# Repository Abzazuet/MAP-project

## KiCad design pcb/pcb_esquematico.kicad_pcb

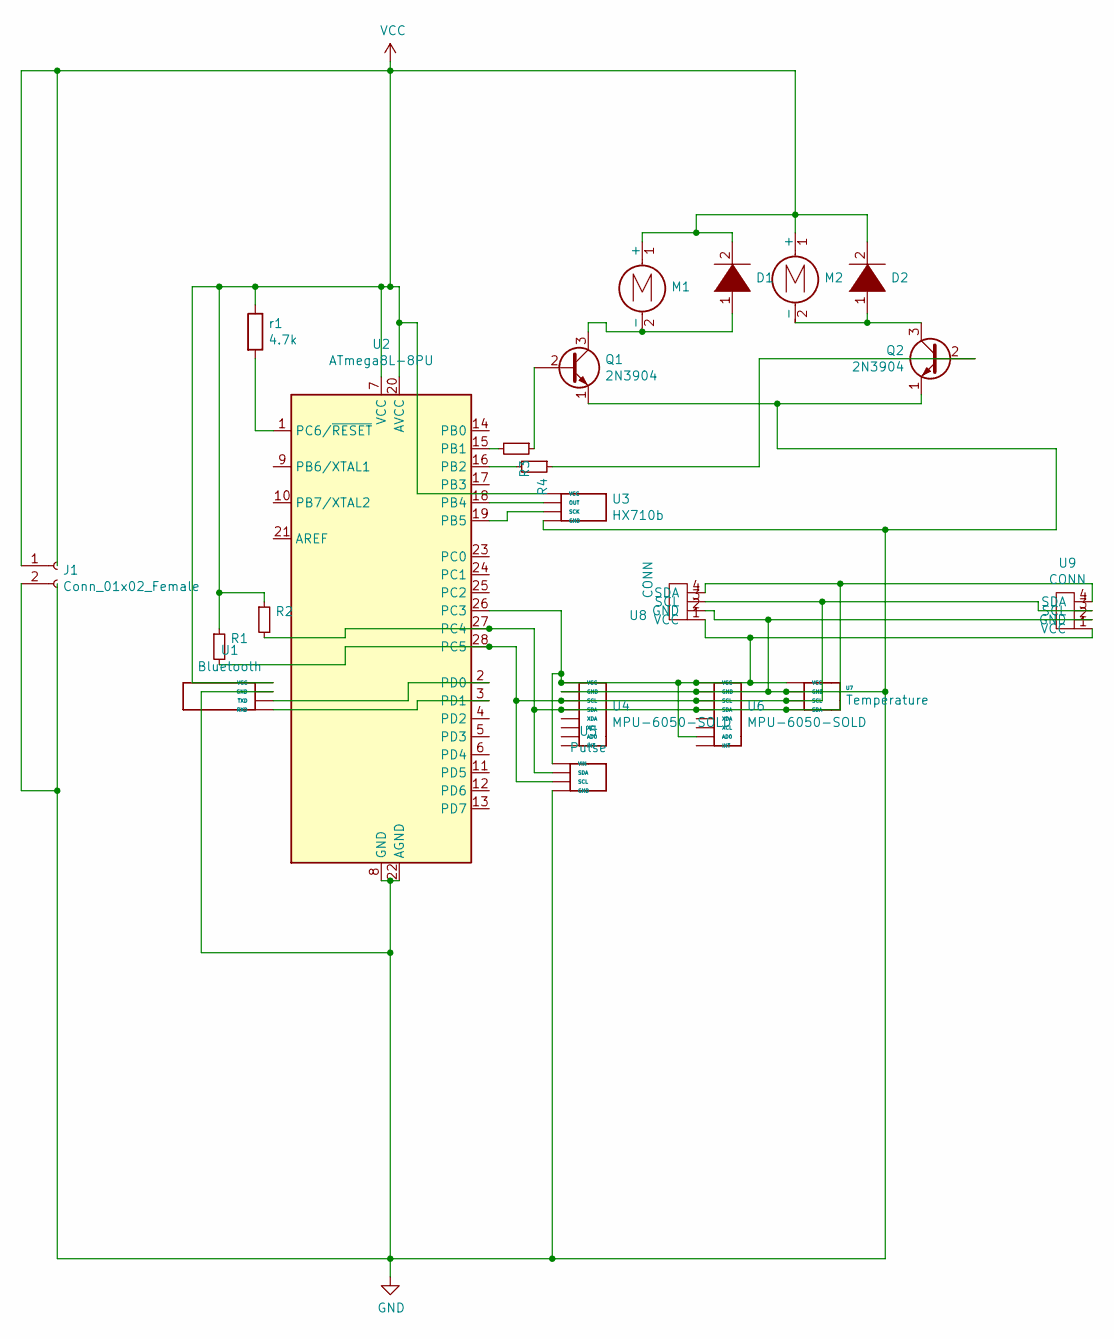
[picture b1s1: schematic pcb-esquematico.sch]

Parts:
D1: DIODE; D_DO-41_SOD81_P5.08mm_Vertical_KathodeUp
D2: DIODE; D_DO-41_SOD81_P5.08mm_Vertical_AnodeUp
J1: Conn_01x02_Female; JWT_A3963_1x02_P3.96mm_Vertical
M1, M2: Motor_DC; PinHeader_1x02_P2.54mm_Horizontal
Q1, Q2: 2N3904; TO-92_HandSolder
R1, R2: 4700; R_Axial_DIN0309_L9.0mm_D3.2mm_P12.70mm_Horizontal
R3, R4: 1000; R_Axial_DIN0309_L9.0mm_D3.2mm_P12.70mm_Horizontal
U1: Bluetooth; PinHeader_1x04_P2.54mm_Vertical
U2: ATmega8L-8PU; DIP-28_W7.62mm
U3: HX710b; PinHeader_1x04_P2.54mm_Vertical
U4, U6: MPU-6050-SOLD; PinHeader_1x08_P2.54mm_Vertical
U5: Pulse; PinHeader_1x04_P2.54mm_Vertical
U7: Temperature; PinHeader_1x04_P2.54mm_Vertical
U8, U9: CONN; PinSocket_1x04_P2.54mm_Horizontal
r1: 4.7k; R_Axial_DIN0309_L9.0mm_D3.2mm_P12.70mm_Horizontal

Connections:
GND: J1.2, Q1.1 (E), Q2.1 (E), U1.2 (GND), U2.8 (GND), U2.22 (AGND), U3.4 (GND), U4.2 (GND), U5.4 (GND), U6.2 (GND), U7.2 (GND), U8.2 (GND), U9.2 (GND)
unnamed: D1.1 (K), M1.2 (-), Q1.3 (C)
unnamed: D2.1 (K), M2.2 (-), Q2.3 (C)
unnamed: Q1.2 (B), R3.1
unnamed: Q2.2 (B), R4.1
unnamed: R1.2, U2.28 (PC5), U4.3 (SCL), U5.3 (SCL), U6.3 (SCL), U7.3 (SCL), U8.3 (SCL), U9.3 (SCL)
unnamed: R2.2, U2.27 (PC4), U4.4 (SDA), U5.2 (SDA), U6.4 (SDA), U7.4 (SDA), U8.4 (SDA), U9.4 (SDA)
unnamed: R3.2, U2.15 (PB1)
unnamed: R4.2, U2.16 (PB2)
unnamed: U1.3 (TXD), U2.2 (PD0)
unnamed: U1.4 (RXD), U2.3 (PD1)
unnamed: U2.1 (PC6/~RESET), r1.2
unnamed: U2.18 (PB4), U3.2 (OUT)
unnamed: U2.19 (PB5), U3.3 (SCK)
unnamed: U2.26 (PC3), U4.1 (VCC), U5.1 (VIN), U6.1 (VCC), U6.7 (AD0), U7.1 (VCC), U8.1 (VCC), U9.1 (VCC)
VCC: D1.2 (A), D2.2 (A), J1.1, M1.1 (+), M2.1 (+), R1.1, R2.1, U1.1 (VCC), U2.7 (VCC), U2.20 (AVCC), U3.1 (VCC), r1.1

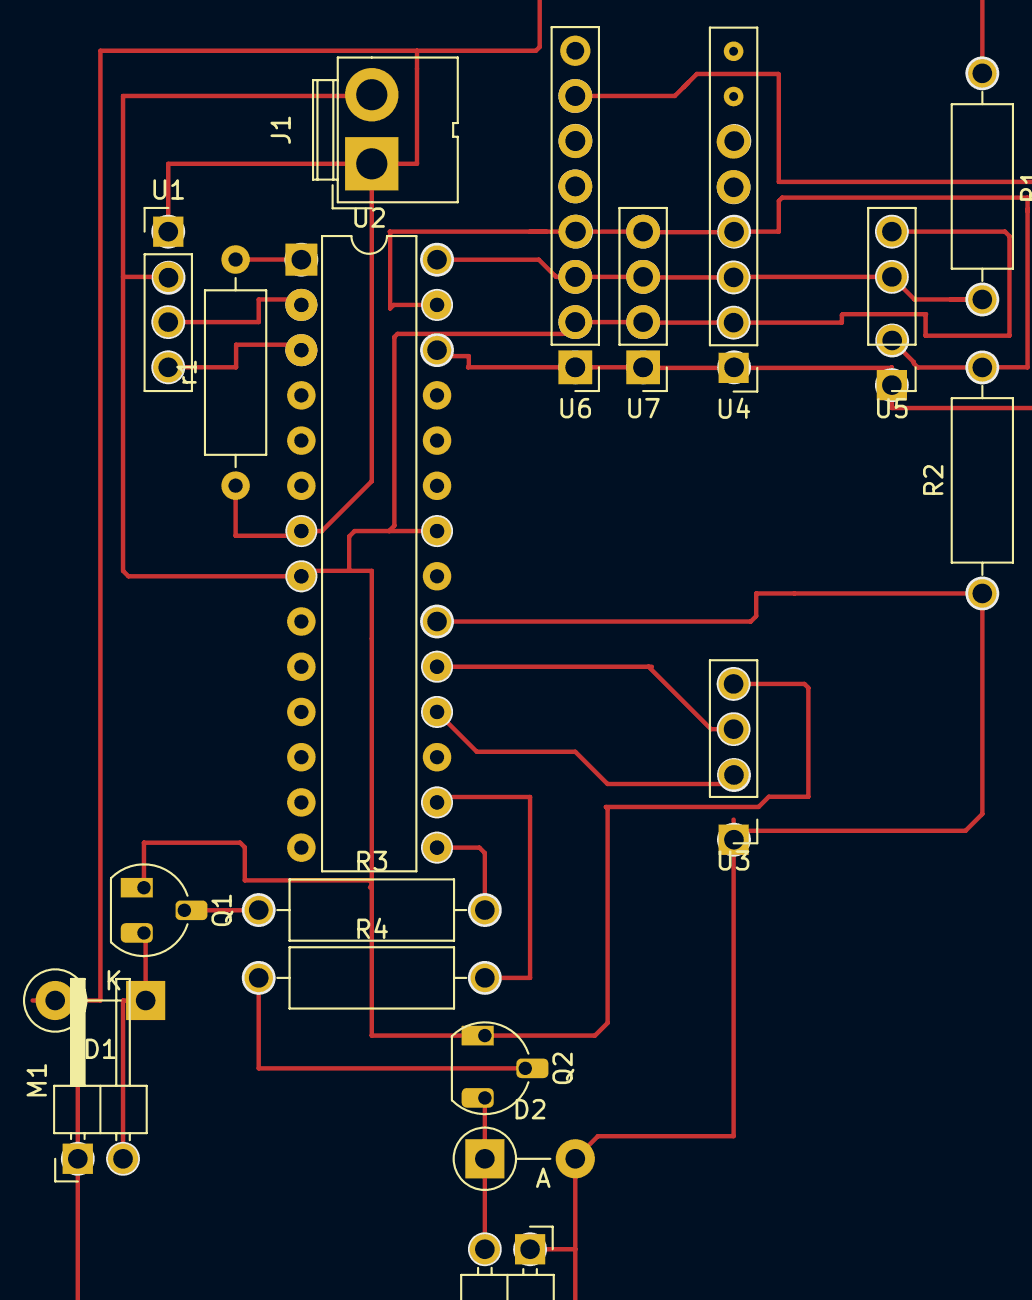
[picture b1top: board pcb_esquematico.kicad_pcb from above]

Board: 2 copper layers, 19 parts (0 on the bottom side), 16 nets.

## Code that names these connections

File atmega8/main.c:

#include <avr/io.h>						//Necesaria para registros
#include <avr/interrupt.h>				//Necesaria para interrupciones
#include <util/delay.h>					//Pausas de tiempo
#include <stdint.h> 					//Librerica para comunicacion uart
#include<string.h>						//Manipular cadenas caracteres
#include<stdio.h>						//Modificar entradas i salidas de texto
#include <stdlib.h>						//Concatenar registros de ADC

#define FOSC 1000000					//Definir frecuencia de oscilacion
#define SCL 31250						//Frecuencia SCL
#define BAUD 9600						//Baudios de comunicacion
#define MYUBRR FOSC/8/BAUD-1			//COnstante para establecer 9600 en nregistro, error de 0.2
#define HX711_MODERUNNING 1
#define HX711_MODECALIBRATION1OF2 2
#define HX711_MODECALIBRATION2OF2 3
#define HX711_MODECURRENT 1
#define TAMANIO 30
#define TAMANIOARRAY 30

#include "USART.c"
#include "I2C.c"
#include "Giroscopio.c"
#include "Giroscopio2.c"
#include "PWM.c"
#include "ADC.c"

#include "hx711.c"
#include "Temperatura.c"
#include "Oximetro.c"


char dato, buffer1[TAMANIO],buffer2[TAMANIO],buffer3[TAMANIO],buffer4[TAMANIO],float_[10];				//Variable de que almacena dato recibido, variable que transmite dato, variable conversion
uint8_t presion, presion1, presion2, oscilacion;
uint8_t presiones[TAMANIOARRAY], oscilaciones[TAMANIOARRAY];

void PIO_Init(){						//Declarar pines de salida y entrada
	DDRB |=(1<<PB2);					//Salida PWM OC1B
	DDRB |=(1<<PB1);					//Salida PWM OC1A
	DDRB |=(1<<PB5);					//Salida SCK
	DDRC |=(1<<PC3);					//Pin de control de sensores
	PORTC |=(1<<PC3);					//Inicio de sensores apagados
}

void Inflar(){
	OCR1A=31;
	OCR1B=31;
}

void Parar(){
	OCR1A=0;
}

void Cerrar(){
	OCR1B=31;
}

void Abrir(){
	OCR1B=0;
}

void TomarPresiones(){
	presion1=Pres_Read();
	presion=presion1;
	presion2=Pres_Read();
	oscilacion=presion1-presion2;
}

int main (void)							//Main 
{
	PIO_Init();							//Configuracion Puertos
	I2C_Init();							//Configuracion I2C
	USART_Init(MYUBRR);					//Configuracion Serial	
	ADC_Init();							//Configuracion ADC
	PWM_Init();							//Configuracion PWM
	hx711_init(HX711_GAINCHANNELA128, 10000, 9850000);			//Configuracion Presion		
	while(1)							//Bucle para que este funcionando indeterminadamente
	{
		dato=RecibirBT();				//Recepcion de dato enviado por eñ celular
		if (dato=='m'){
			_delay_ms(5000);					//Iniciar medicion
			//Paso 2: Inflar brazalete y tomar presiones
			presion = 0;			//Lectura de presion
			Inflar();
			_delay_ms(4000);	
			uint8_t i=0;
			while(presion < 160){				//Hacer hasta que llegue a 160mmHg
				presion = Pres_Read();		//Lectura para saber cambio en presion
			}
			//Paso 3: Parar el motor y se comienza a desinlfar, comienza metodo osculatorio
			Parar();						//Desactivar motor y mantener valvula cerrada
			while(presion > 50){				//Hacer hasta que la presion sea menor a 50 mmHg
				TomarPresiones();			//Tomar presion dos veces y compararlas para saber oscilacion
				if(oscilacion<2 && oscilacion>=1){			//Comprobar oscilacion tres veces
					presiones[i]=(presion1+presion2)/2;	//Guardar el promedio de ambas presiones en el arreglo
					oscilaciones[i]=oscilacion;			//Guardar oscilacion
					i++;					//Aumentar indice de guardado
				}
				presion=Pres_Read();
				while(presion>presion1-2){	//Terminado el proceso, comenzar a desinglar hasta que la presion decremente 5
					presion=Pres_Read();
				}
				Cerrar();					//Cerrar valvula para nuevo comienzo
			}
			Abrir();						//Abrir por completo
			//Paso 4: determinacion de presiones siastole y diastole
			uint8_t sys=0, dys=0, mayor=0, menor=0;
			for (uint8_t i=0; i<TAMANIOARRAY; i++){			//Recorrer todo el vector
				if (presiones[mayor]<=presiones[i]){		//La presion mas grande es sistolica
					sys=presiones[i];						//Guardar valor
					mayor=i;
				}
				if (presiones[menor]>=presiones[i] && presiones[i]!=0){		//La presion mas baja es la diastole
					dys=presiones[i];		//Guardar valor
					menor=i;
				}
			}

			sys = 125;
			dys = 74;			
			dtostrf(sys, 3, 0, float_ );
			sprintf(buffer1,"%s mmHg",float_);
			dtostrf(dys, 3, 0, float_ );
			sprintf(buffer2,"%s mmHg",float_);
			pulso = 76;
			celcius = 36.4;
			dtostrf(pulso, 3, 0, float_ );
			sprintf(buffer3,"%s ppm",float_);
			dtostrf(celcius,2,2,float_);
			sprintf(buffer4,"%s C",float_);
			//Paso 5: enviar datos por medio de bluetooth

			/*Enviar sistole, diastole, pulso y temperatura*/
			charToUint8Send(buffer1);
			charToUint8Send(buffer2);
			charToUint8Send(buffer3);
			charToUint8Send(buffer4);
		}
		else if (dato=='p'){
			Inflar();
			_delay_ms(4000);
			presion = Pres_Read();
			while (1){
				presion = Pres_Read();
				dtostrf(presion, 3, 0, float_ );
				sprintf(buffer1,"%s mmHg",float_);
				charToUint8Send(buffer1);
			}
		}

			else{}
	}
}

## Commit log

2021-11-09 First template
